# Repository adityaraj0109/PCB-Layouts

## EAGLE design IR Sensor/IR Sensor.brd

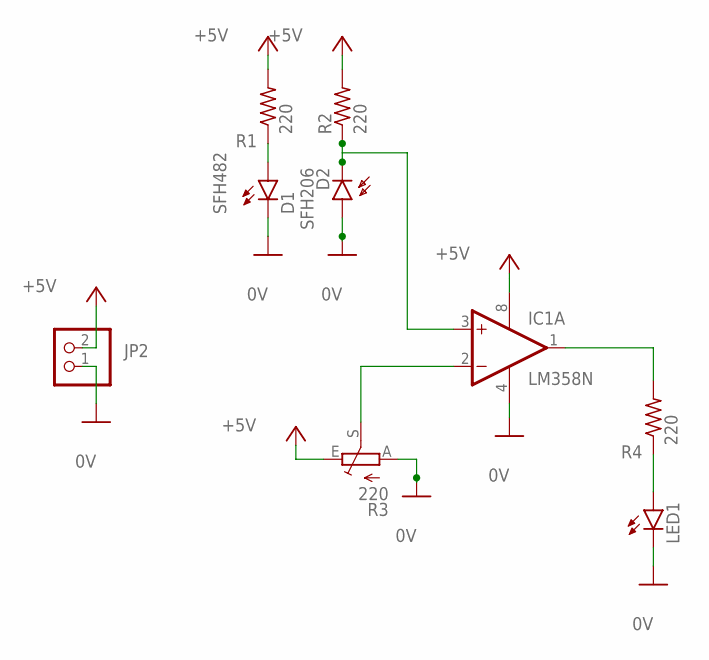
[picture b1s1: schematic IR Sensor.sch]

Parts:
D1: SFH482
D2: SFH206
IC1: LM358N; DIL08
JP2: PINHD-1X2; 1X02
LED1: LED5MM
R1, R2, R4: 220; 0207/10
R3: 220; CA6V

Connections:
0V: D1.K (C), D2.A, IC1.4 (V-), JP2.1, LED1.K (C), R3.A
+5V: IC1.8 (V+), JP2.2, R1.2, R2.2, R3.E
unnamed: IC1.1 (OUT), R4.2
unnamed: LED1.A, R4.1
unnamed: D1.A, R1.1
unnamed: D2.K (C), IC1.3 (+IN), R2.1
unnamed: IC1.2 (-IN), R3.S

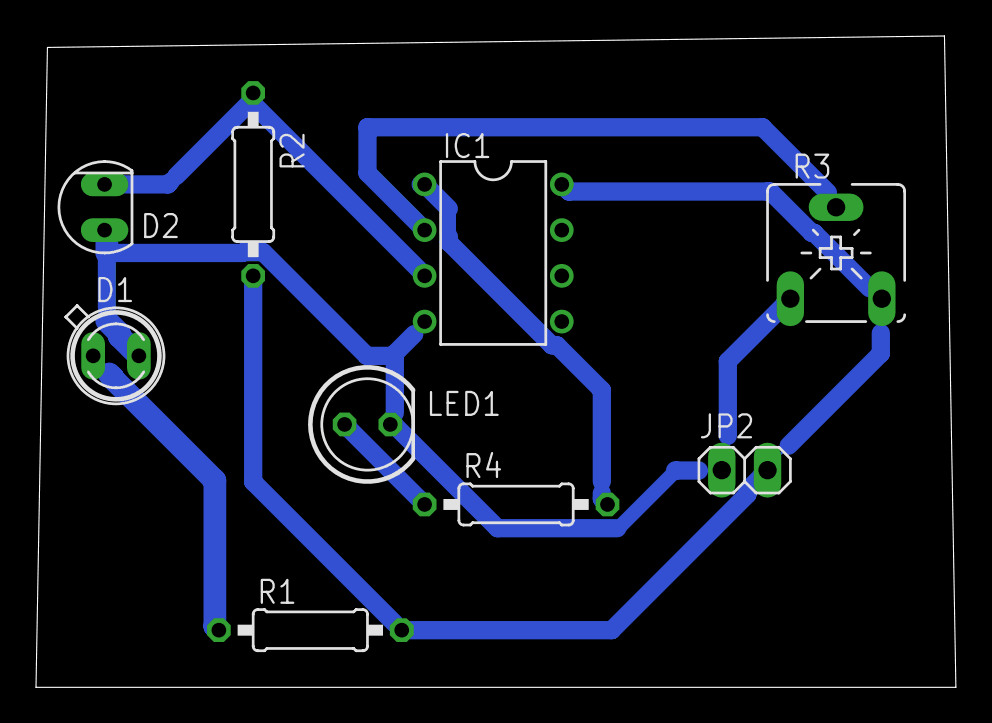
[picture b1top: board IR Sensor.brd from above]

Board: 2 copper layers, 51.1 x 36.2 mm, 9 parts (0 on the bottom side), 7 nets.

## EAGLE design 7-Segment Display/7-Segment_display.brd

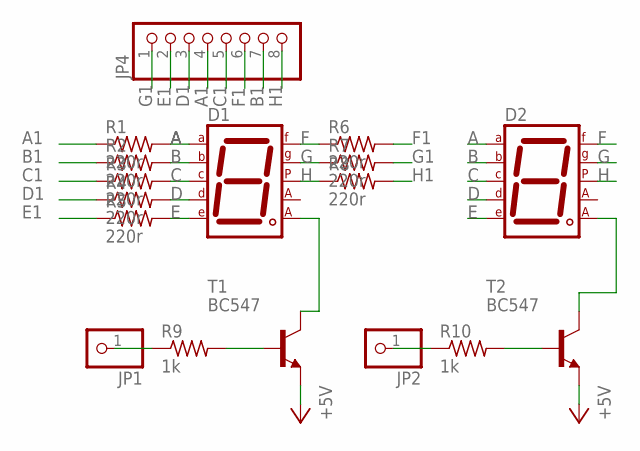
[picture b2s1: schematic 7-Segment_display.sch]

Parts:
D1, D2: 7SEG-CA; 7SEG-13
JP1, JP2: PINHD-1X1; 1X01
JP4: PINHD-1X8; 1X08
R1, R2, R3, R4, R5, R6, R7, R8: 220r; 0207/10
R9, R10: 1k; 0207/10
T1, T2: BC547; TO92

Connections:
+5V: T1.1 (E), T2.1 (E)
A: D1.7 (A), D2.7 (A), R1.2
A1: JP4.4, R1.1
B: D1.6 (B), D2.6 (B), R2.2
B1: JP4.7, R2.1
C: D1.4 (C), D2.4 (C), R3.2
C1: JP4.5, R3.1
D: D1.2 (D), D2.2 (D), R4.2
D1: JP4.3, R4.1
E: D1.1 (E), D2.1 (E), R5.2
E1: JP4.2, R5.1
F: D1.9 (F), D2.9 (F), R6.1
F1: JP4.6, R6.2
G: D1.10 (G), D2.10 (G), R7.1
G1: JP4.1, R7.2
H: D1.5 (DP), D2.5 (DP), R8.1
H1: JP4.8, R8.2
unnamed: R9.2, T1.2 (B)
unnamed: D1.8 (CA2), T1.3 (C)
unnamed: R10.2, T2.2 (B)
unnamed: D2.8 (CA2), T2.3 (C)
unnamed: JP1.1, R9.1
unnamed: JP2.1, R10.1

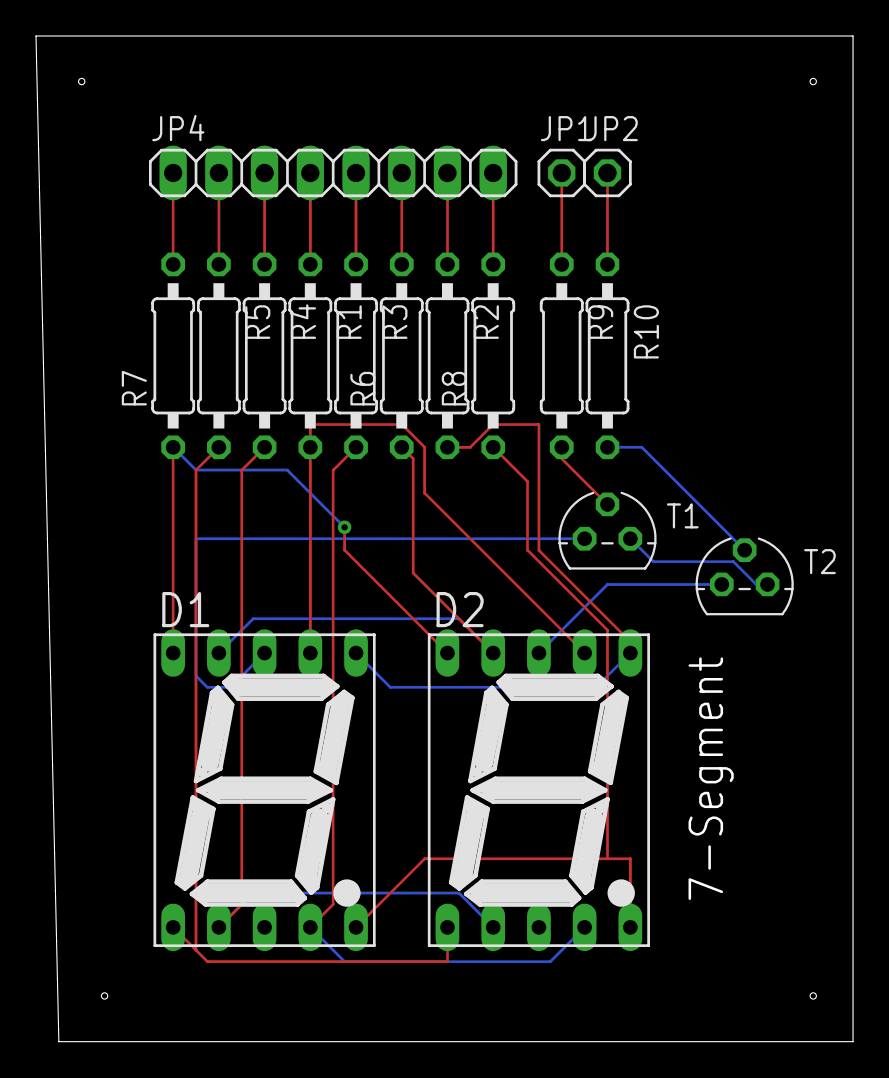
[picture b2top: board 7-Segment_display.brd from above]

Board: 2 copper layers, 45.4 x 55.9 mm, 17 parts (0 on the bottom side), 23 nets.

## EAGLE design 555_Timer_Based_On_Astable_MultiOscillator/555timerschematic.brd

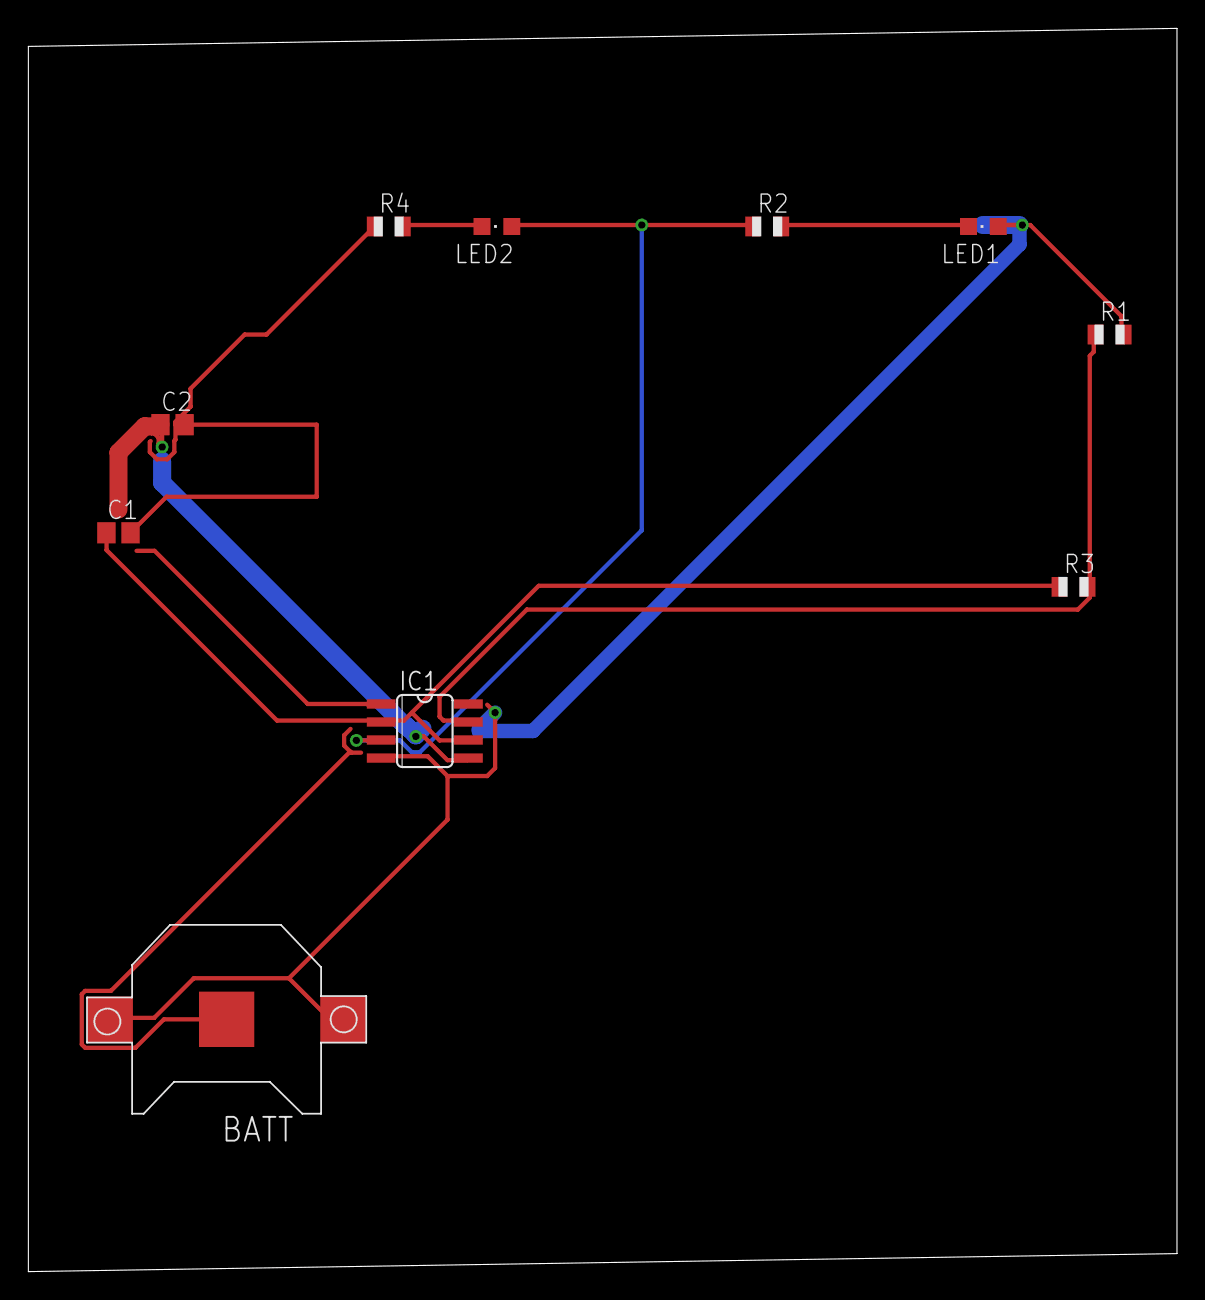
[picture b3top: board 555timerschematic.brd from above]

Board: 2 copper layers, 80.9 x 87.6 mm, 10 parts (0 on the bottom side), 8 nets.

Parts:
BATT: CR1220; CR1220-SMD
C1: 22uF; C0805
C2: 0.01uF; C0805
IC1: LM555D; SO08
LED1, LED2: green; CHIPLED_0805
R1, R3: 1k; R0805
R2, R4: 100; R0805

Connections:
CONN: C1.1, IC1.2, IC1.6, R3.1
GND: BATT.-, C1.2, C2.2, IC1.1, R4.1
unnamed: LED1.C, R2.2
unnamed: IC1.3, LED2.A, R2.1
unnamed: LED2.C, R4.2
unnamed: IC1.7, R1.1, R3.2
unnamed: C2.1, IC1.5
VCC: BATT.+$1, BATT.+$2, IC1.4, LED1.A, R1.2

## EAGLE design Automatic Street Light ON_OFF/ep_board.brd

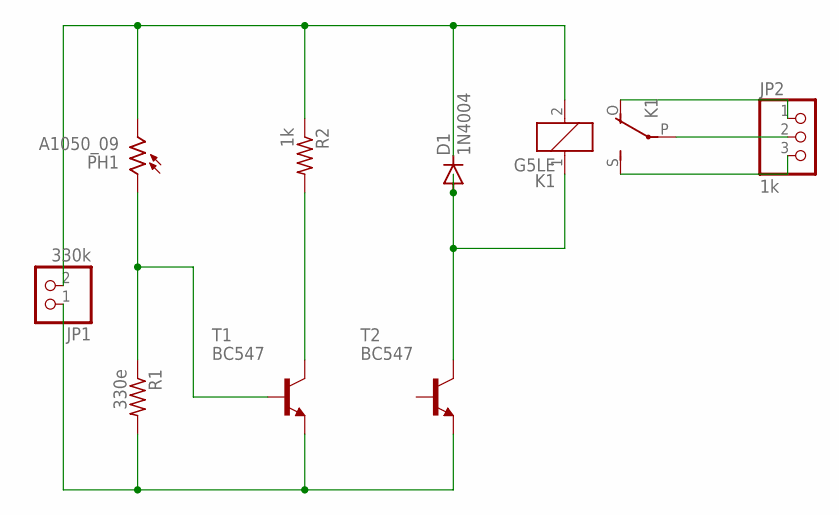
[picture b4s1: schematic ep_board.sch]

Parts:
D1: 1N4004; DO41-10
JP1: 330k; 1X02
JP2: 1k; 1X03
K1: G5LE
PH1: A1050_09; T0-46-A10XX
R1: 330e; 0207/10
R2: 1k; 0207/10
T1, T2: BC547; TO92

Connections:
unnamed: JP2.2, K1.P
unnamed: D1.C, JP1.2, K1.2, PH1.2, R2.1
unnamed: PH1.1, R1.1, T1.2 (B)
unnamed: JP1.1, R1.2, T1.1 (E), T2.1 (E)
unnamed: R2.2, T1.3 (C)
unnamed: D1.A, K1.1, T2.3 (C)
unnamed: JP2.3, K1.S
unnamed: JP2.1, K1.O

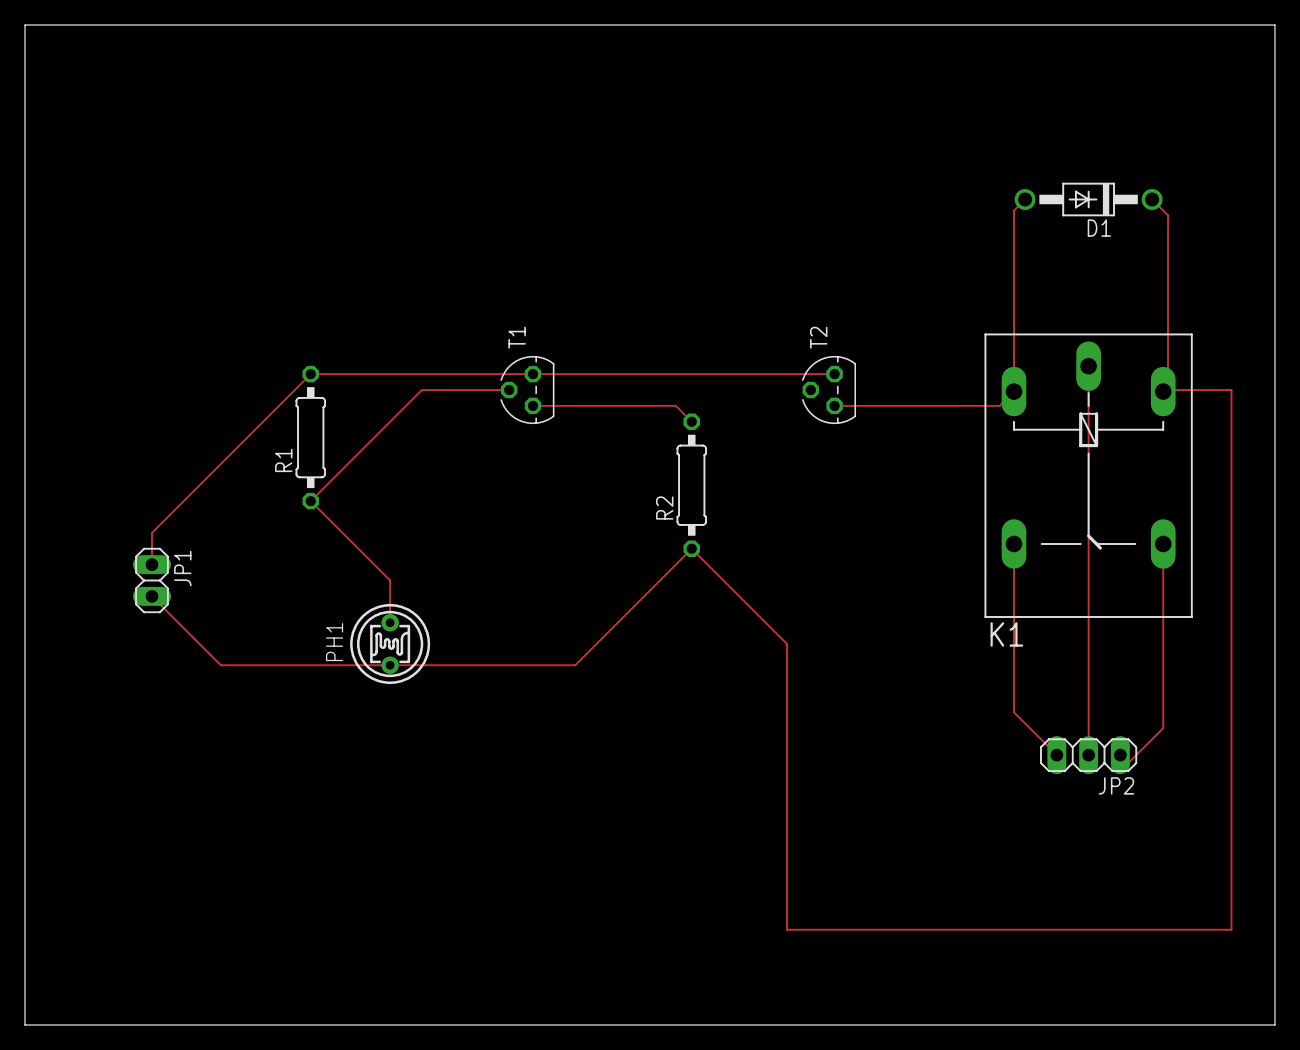
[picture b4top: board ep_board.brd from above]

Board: 2 copper layers, 100.0 x 80.0 mm, 9 parts (0 on the bottom side), 8 nets.

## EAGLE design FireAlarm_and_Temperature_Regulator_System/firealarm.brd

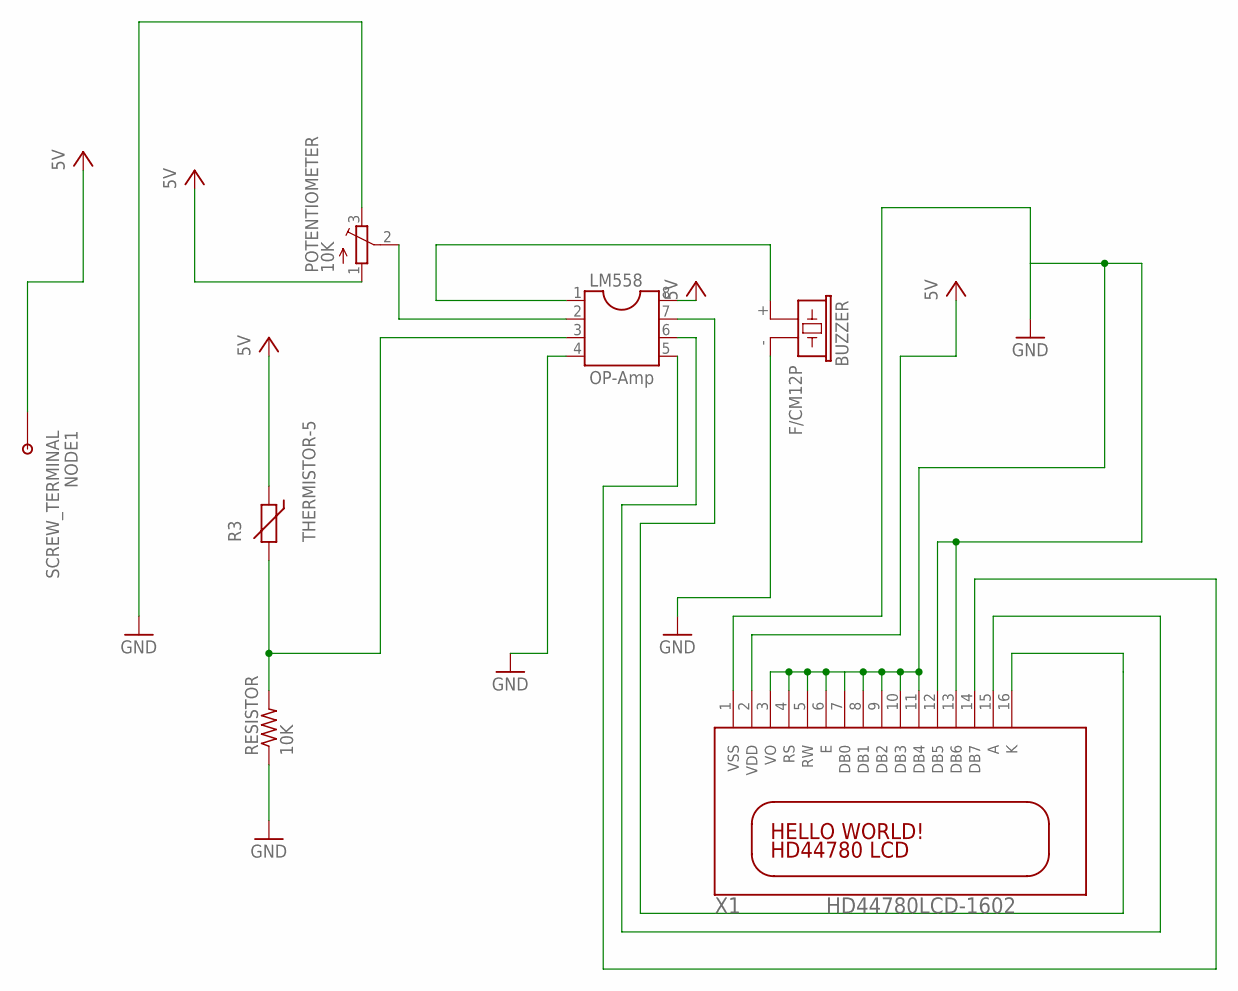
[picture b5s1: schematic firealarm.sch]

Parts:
BUZZER: F/CM12P
LM558: OP-Amp; SOCKET-08
NODE1: SCREW_TERMINAL; NINIGI_PCB_1M4
POTENTIOMETER: 10K; 3223G
R3: THERMISTOR-5; R-5
RESISTOR: 10K; 0204V
X1: HD44780LCD-1602; LCD1602

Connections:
GND: BUZZER.- (2), LM558.4, POTENTIOMETER.3 (E), RESISTOR.1, X1.1 (VSS), X1.3 (VO), X1.4 (RS), X1.5 (RW), X1.6 (E), X1.8 (DB1), X1.9 (DB2), X1.10 (DB3), X1.11 (DB4), X1.12 (DB5), X1.13 (DB6)
unnamed: BUZZER.+ (1), LM558.1
unnamed: LM558.3, R3.2, RESISTOR.2
unnamed: LM558.2, POTENTIOMETER.2 (S)
unnamed: LM558.7, X1.16 (K)
unnamed: LM558.5, X1.14 (DB7)
unnamed: LM558.6, X1.15 (A)
VCC: LM558.8, NODE1.1, NODE1.2, NODE1.3, NODE1.4, NODE1.C, POTENTIOMETER.1 (A), R3.1, X1.2 (VDD)

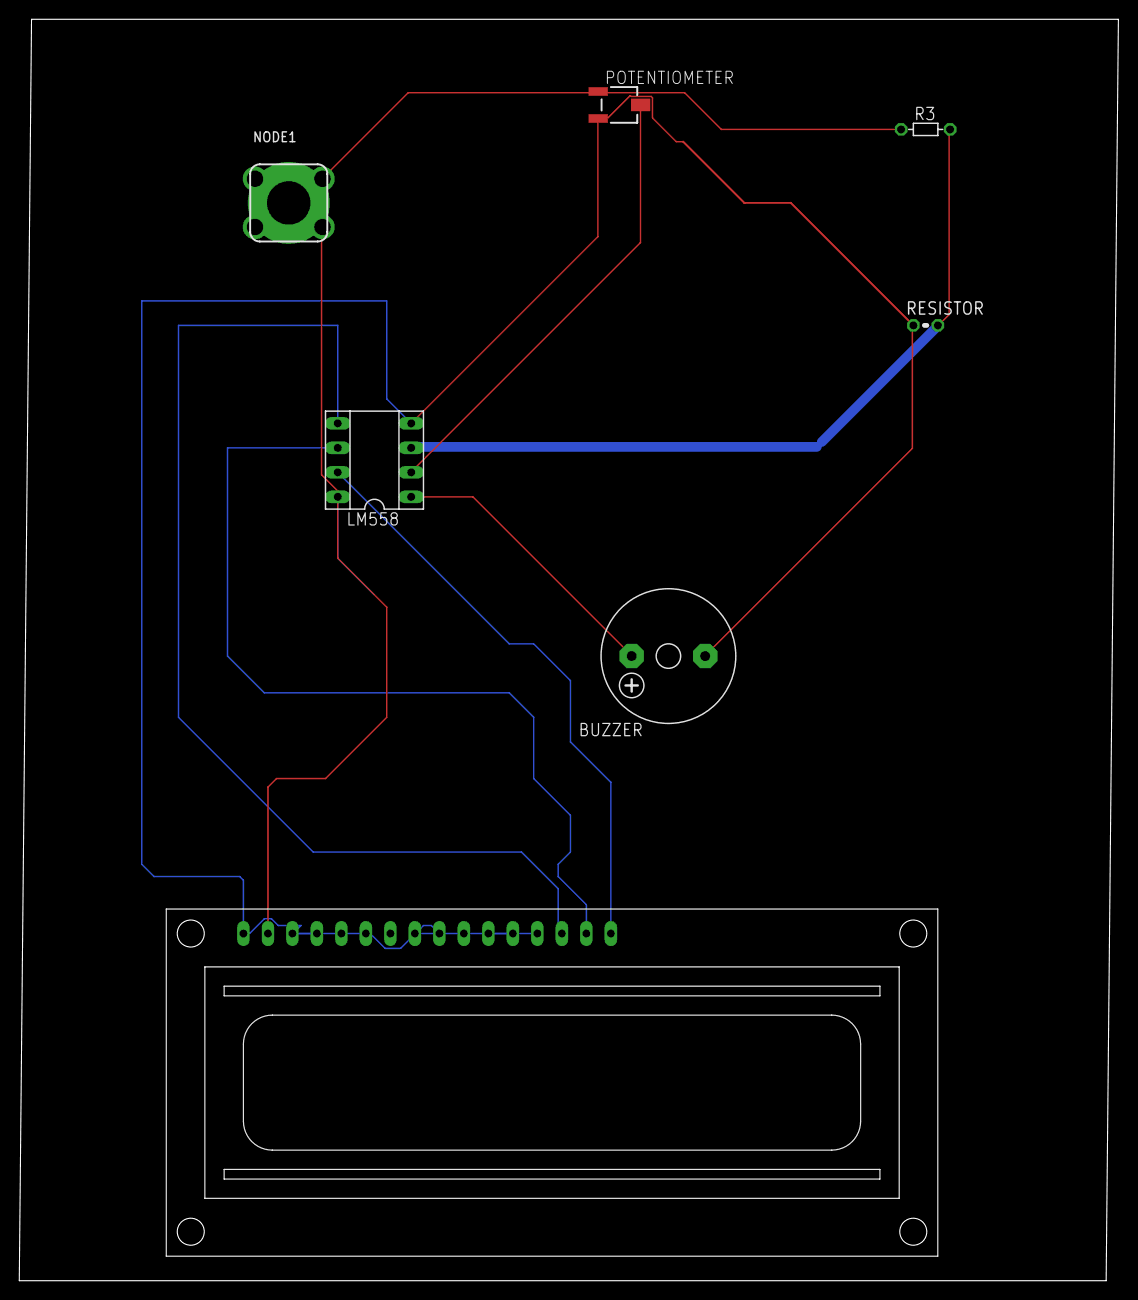
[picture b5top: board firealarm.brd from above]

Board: 2 copper layers, 114.0 x 130.8 mm, 7 parts (0 on the bottom side), 8 nets.
